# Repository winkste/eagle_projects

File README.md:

# eagle_projects
eagle projects for several different targets

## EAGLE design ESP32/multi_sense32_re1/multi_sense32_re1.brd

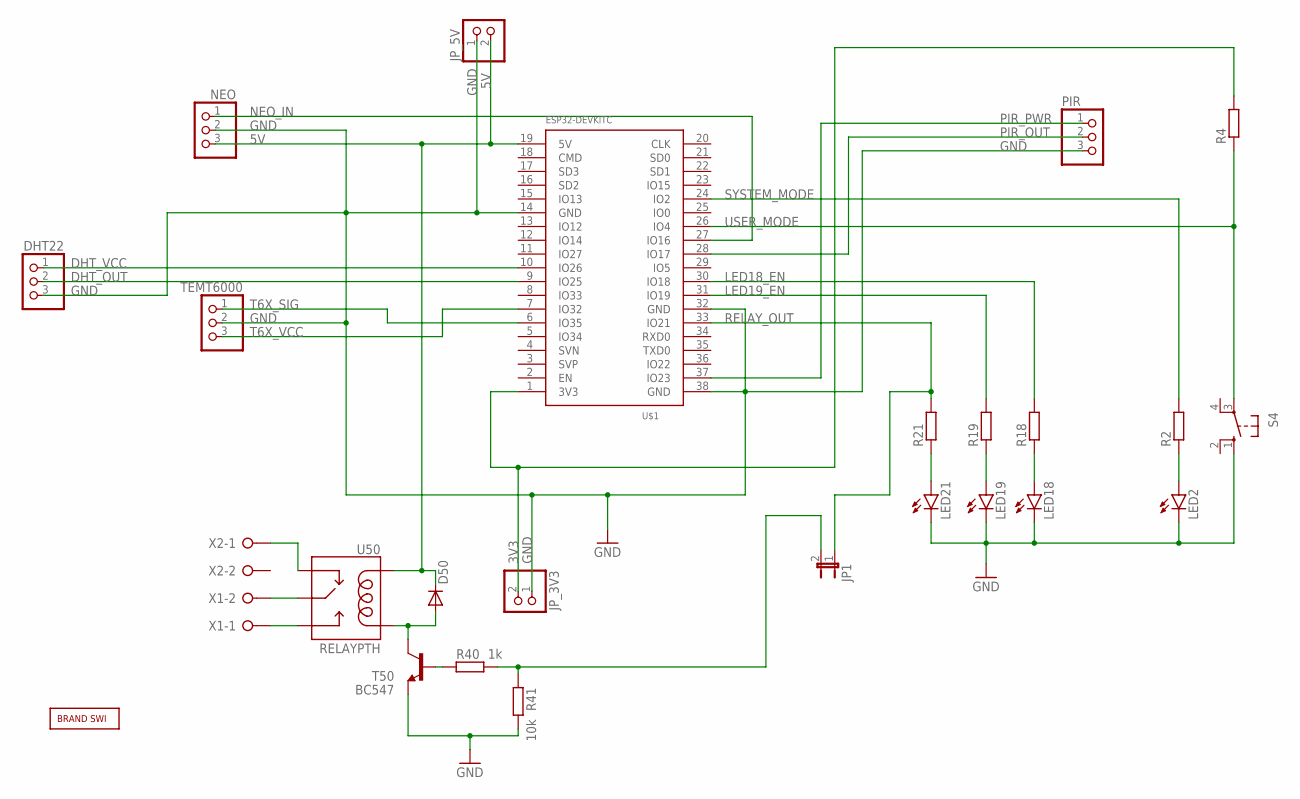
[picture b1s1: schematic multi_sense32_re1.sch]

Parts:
D50: 1N4148DO35-7; DO35-7
DHT22: PINHD-1X3; 1X03
JP1: JP1E; JP1
JP_3V3, JP_5V: PINHD-1X2; 1X02
LED2, LED18, LED19, LED21: LEDCHIPLED_1206; CHIPLED_1206
NEO: PINHD-1X3; 1X03
PIR: PINHD-1X3; 1X03
R2, R4, R18, R19, R21: R-EU_R1206; R1206
R40: 1k; 0207/10
R41: 10k; 0207/10
S4: 10-XX; B3F-10XX
T50: BC547; TO92
TEMT6000: PINHD-1X3; 1X03
U50: RELAYPTH; SRD-05VDC-SL-C
U$1: ESP32DEVKITC; ESP32-DEVKITC
U$2: BRAND_SWI5X7; BRAND_SWI_5X7
X1, X2: W237-02P; W237-132

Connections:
3V3: JP_3V3.2, R4.2, U$1.1 (3V3)
5V: D50.C, JP_5V.2, NEO.3, U50.COIL1, U$1.19 (5V)
DHT_OUT: DHT22.2, U$1.9 (IO25)
DHT_VCC: DHT22.1, U$1.10 (IO26)
GND: DHT22.3, JP_3V3.1, JP_5V.1, LED2.C, LED18.C, LED19.C, LED21.C, NEO.2, PIR.3, R41.2, S4.1 (S), T50.1 (E), TEMT6000.2, U$1.14 (GND), U$1.32 (GND), U$1.38 (GND)
LED18_EN: R18.2, U$1.30 (IO18)
LED19_EN: R19.2, U$1.31 (IO19)
LED21_EN: JP1.2, R40.2, R41.1
unnamed: U50.SWOPEN, X1.1
unnamed: LED21.A, R21.1
unnamed: U50.SWCOMMON, X1.2
unnamed: LED19.A, R19.1
unnamed: LED18.A, R18.1
unnamed: U50.SWCLOSED (SWCLOSE), X2.1
unnamed: LED2.A, R2.1
unnamed: D50.A, T50.3 (C), U50.COIL0
unnamed: R40.1, T50.2 (B)
NEO_IN: NEO.1, U$1.27 (IO16)
PIR_OUT: PIR.2, U$1.28 (IO17)
PIR_PWR: PIR.1, U$1.37 (IO23)
RELAY_OUT: JP1.1, R21.2, U$1.33 (IO21)
SYSTEM_MODE: R2.2, U$1.24 (IO2)
T6X_SIG: TEMT6000.1, U$1.6 (IO35)
T6X_VCC: TEMT6000.3, U$1.7 (IO32)
USER_MODE: R4.1, S4.3, U$1.26 (IO4)

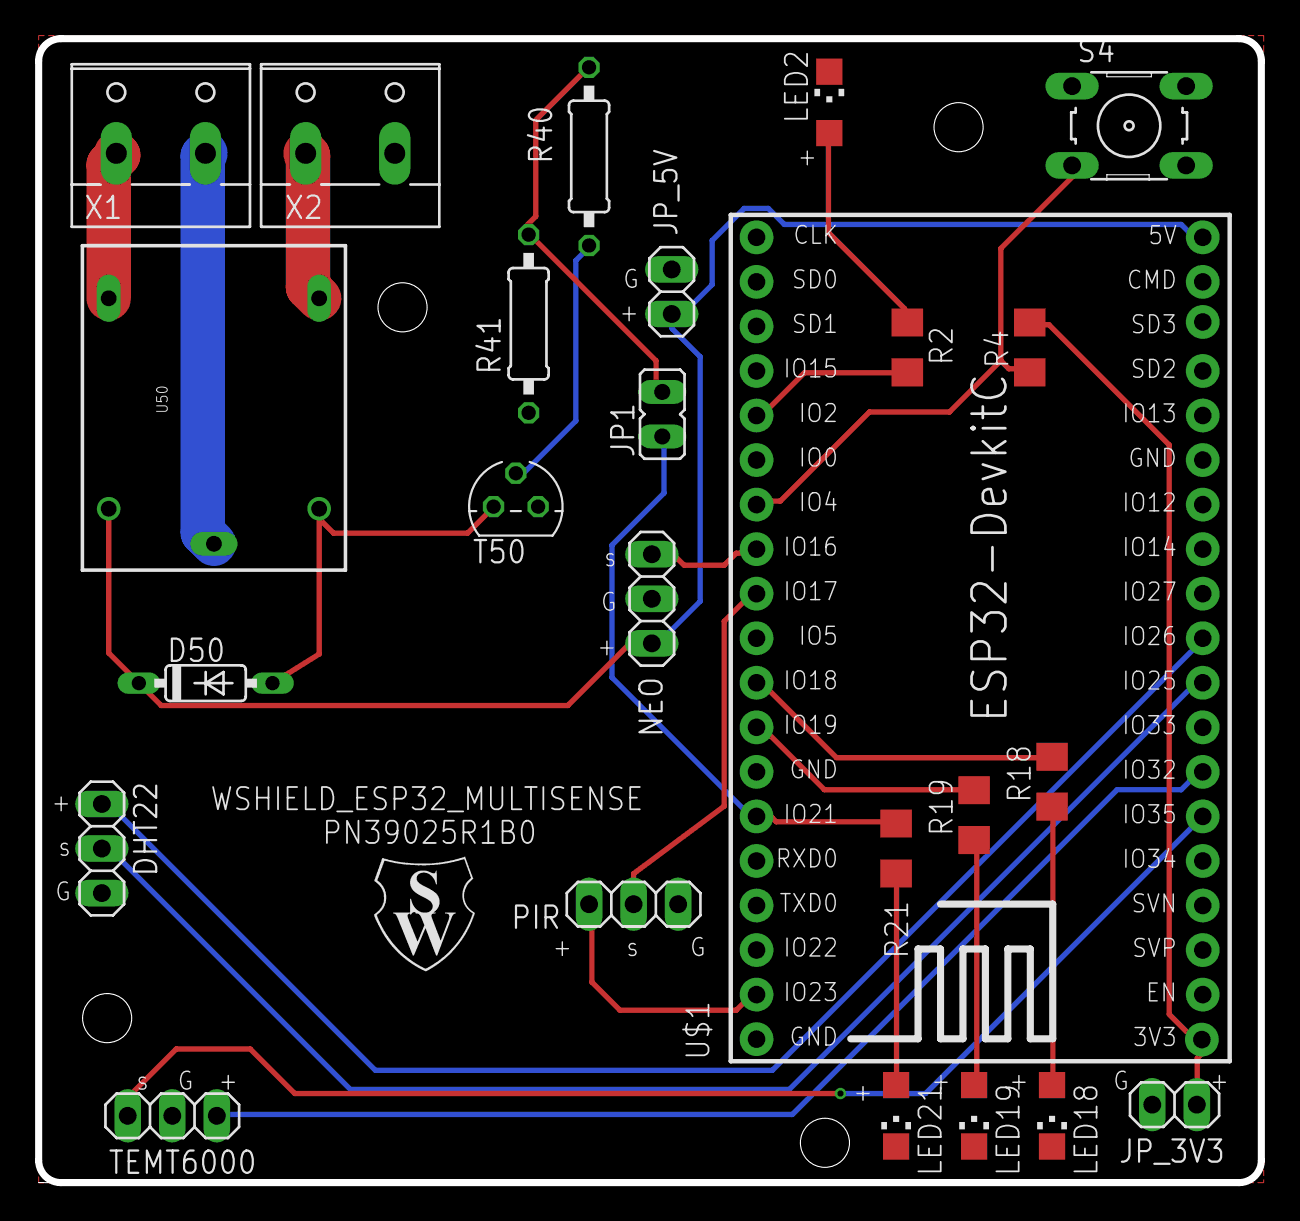
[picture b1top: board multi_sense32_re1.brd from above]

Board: 2 copper layers, 69.7 x 65.2 mm, 26 parts (0 on the bottom side), 25 nets.

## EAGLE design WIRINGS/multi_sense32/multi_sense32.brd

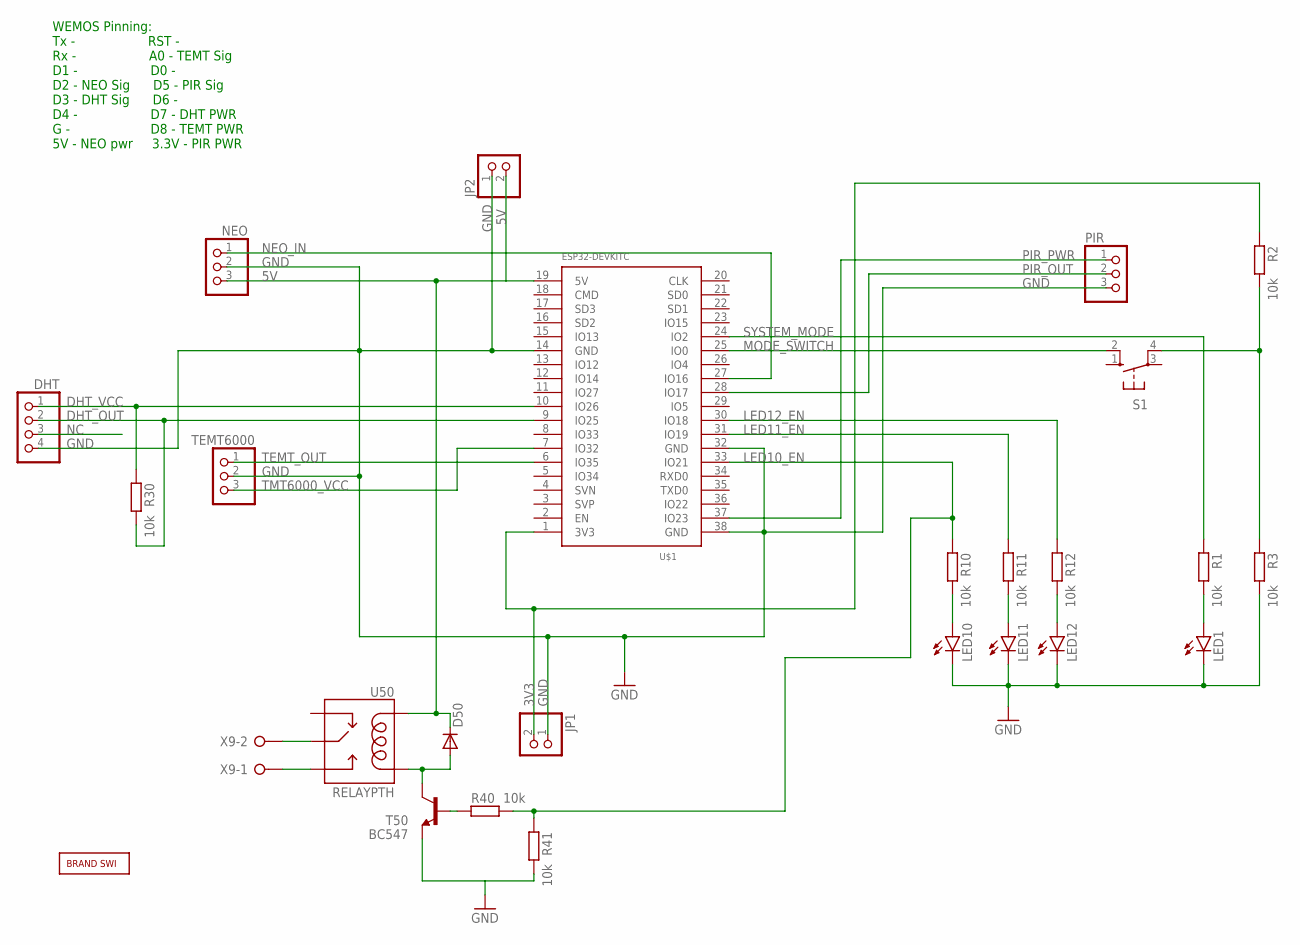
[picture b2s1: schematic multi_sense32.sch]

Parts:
D50: 1N4148DO35-7; DO35-7
DHT: PINHD-1X4; 1X04
JP1, JP2: PINHD-1X2; 1X02
LED1, LED10, LED11, LED12: LED3MM
NEO: PINHD-1X3; 1X03
PIR: PINHD-1X3; 1X03
R1, R2, R3, R10, R11, R12, R30, R40, R41: 10k; 0207/10
S1: 10-XX; B3F-10XX
T50: BC547; TO92
TEMT6000: PINHD-1X3; 1X03
U50: RELAYPTH; SRD-05VDC-SL-C
U$1: ESP32DEVKITC; ESP32-DEVKITC
U$2: BRAND_SWI5X7; BRAND_SWI_5X7
X9: W237-02P; W237-132

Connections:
3V3: JP1.2, R2.1, U$1.1 (3V3)
5V: D50.C, JP2.2, NEO.3, U50.COIL1, U$1.19 (5V)
DHT_OUT: DHT.2, R30.2, U$1.9 (IO25)
DHT_VCC: DHT.1, R30.1, U$1.10 (IO26)
GND: DHT.4, JP1.1, JP2.1, LED1.K (C), LED10.K (C), LED11.K (C), LED12.K (C), NEO.2, PIR.3, R3.2, R41.2, T50.1 (E), TEMT6000.2, U$1.14 (GND), U$1.32 (GND), U$1.38 (GND)
LED10_EN: R10.1, R40.2, R41.1, U$1.33 (IO21)
LED11_EN: R11.1, U$1.31 (IO19)
LED12_EN: R12.1, U$1.30 (IO18)
MODE_SWITCH: S1.2 (S1), U$1.25 (IO0)
unnamed: U50.SWOPEN, X9.1
unnamed: LED10.A, R10.2
unnamed: U50.SWCOMMON, X9.2
unnamed: LED11.A, R11.2
unnamed: LED12.A, R12.2
unnamed: R2.2, R3.1, S1.4 (P1)
unnamed: LED1.A, R1.2
unnamed: D50.A, T50.3 (C), U50.COIL0
unnamed: R40.1, T50.2 (B)
NC: DHT.3
NEO_IN: NEO.1, U$1.27 (IO16)
PIR_OUT: PIR.2, U$1.28 (IO17)
PIR_PWR: PIR.1, U$1.37 (IO23)
SYSTEM_MODE: R1.1, U$1.24 (IO2)
TEMT_OUT: TEMT6000.1, U$1.6 (IO35)
TMT6000_VCC: TEMT6000.3, U$1.7 (IO32)

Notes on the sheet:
WEMOS Pinning: Tx - RST - Rx - A0 - TEMT Sig D1 - D0 - D2 - NEO Sig D5 - PIR Sig D3 - DHT Sig D6 - D4 - D7 - DHT PWR G - D8 - TEMT PWR 5V - NEO pwr 3.3V - PIR PWR

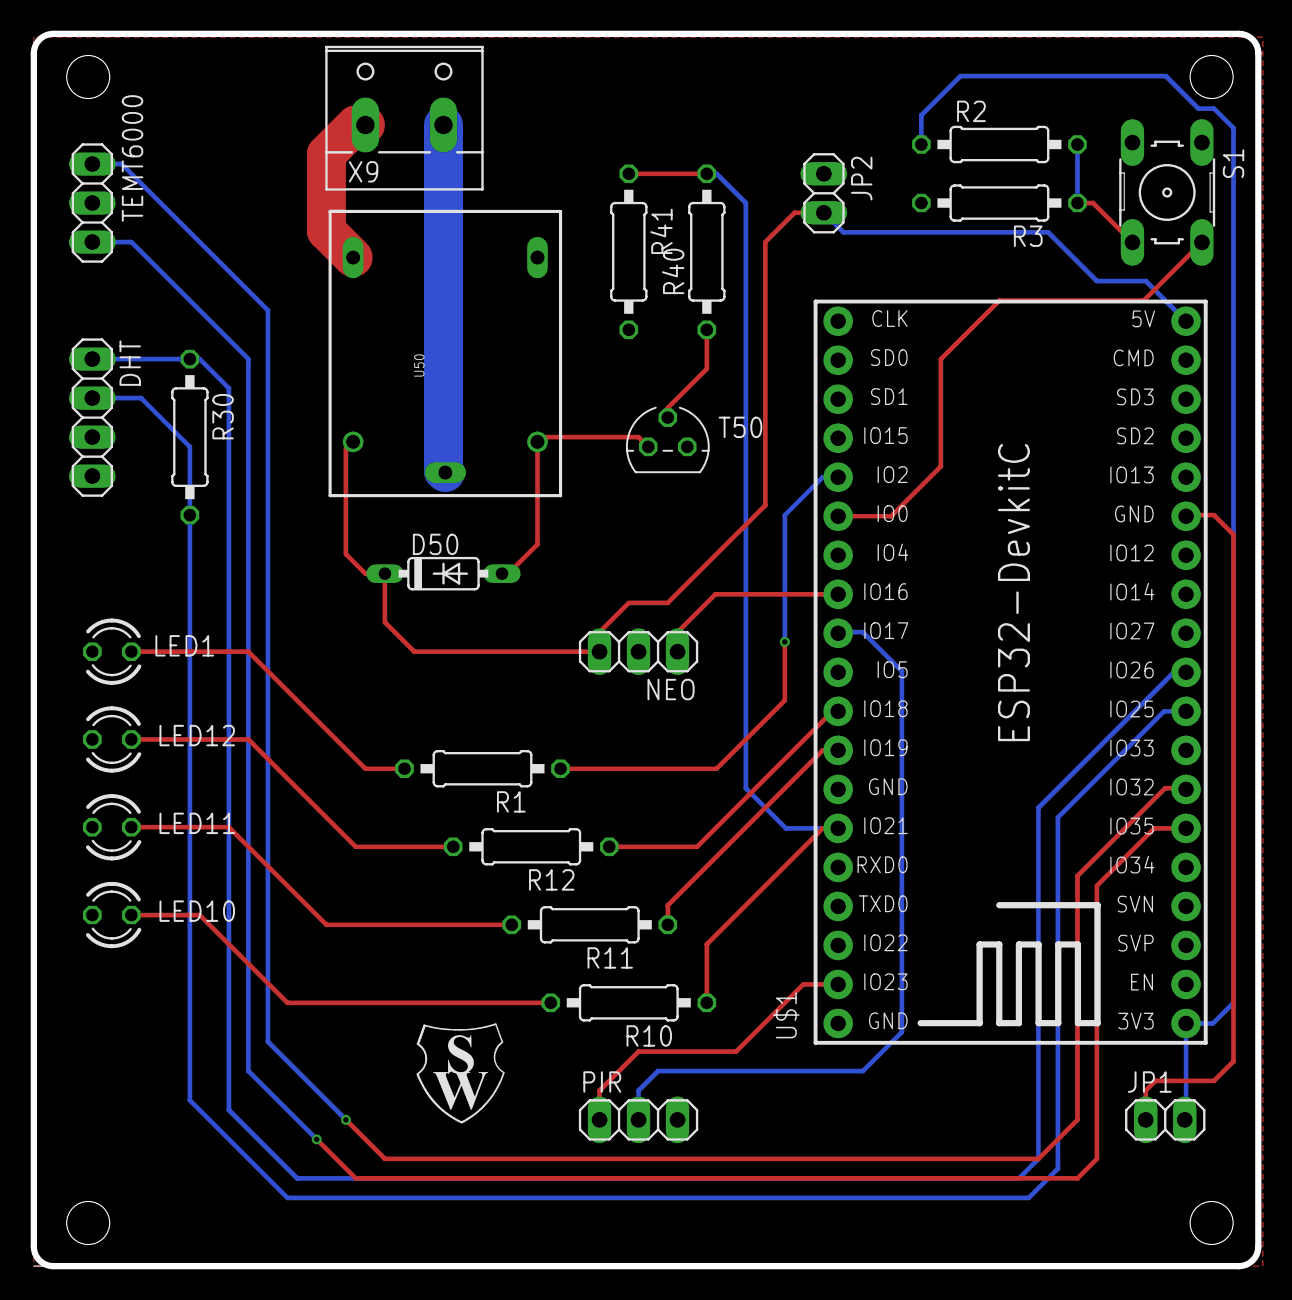
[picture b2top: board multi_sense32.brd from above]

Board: 2 copper layers, 79.7 x 80.2 mm, 26 parts (0 on the bottom side), 24 nets.

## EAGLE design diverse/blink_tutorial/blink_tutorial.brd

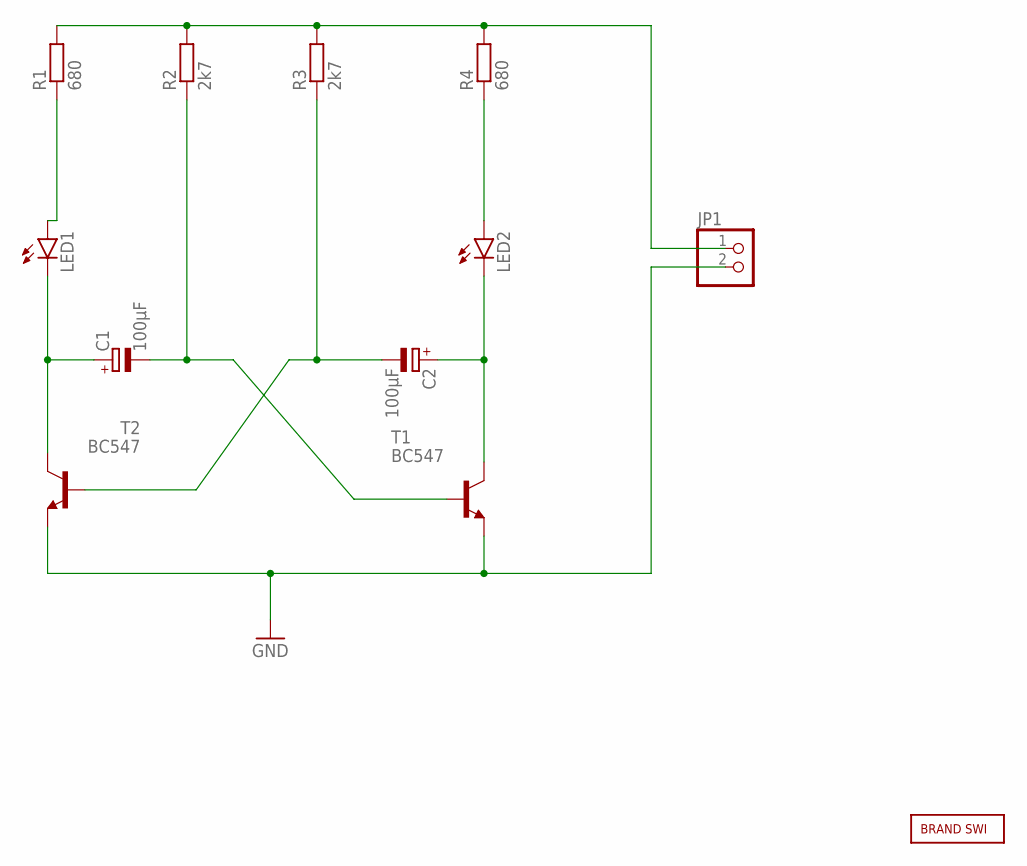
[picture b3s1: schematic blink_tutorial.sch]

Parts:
C1, C2: 100µF; E2,5-6
JP1: PINHD-1X2; 1X02
LED1, LED2: LED5MM
R1, R4: 680; M1206
R2, R3: 2k7; M1206
T1, T2: BC547; TO92
U$1: SIG1; BRAND_SWI_5X7

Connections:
GND: JP1.2, T1.1 (E), T2.1 (E)
unnamed: JP1.1, R1.2, R2.2, R3.2, R4.2
unnamed: LED1.A, R1.1
unnamed: LED2.A, R4.1
unnamed: C1.+, LED1.K (C), T2.3 (C)
unnamed: C2.+, LED2.K (C), T1.3 (C)
unnamed: C2.-, R3.1, T2.2 (B)
unnamed: C1.-, R2.1, T1.2 (B)

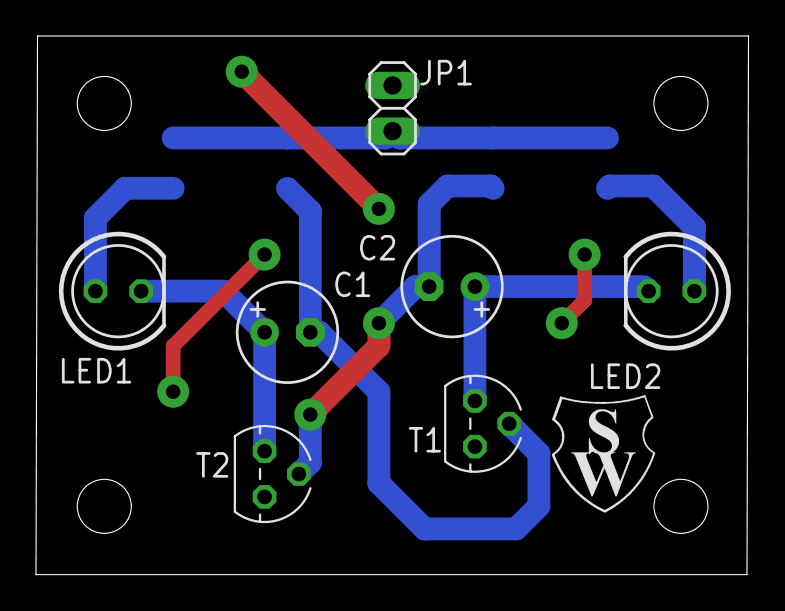
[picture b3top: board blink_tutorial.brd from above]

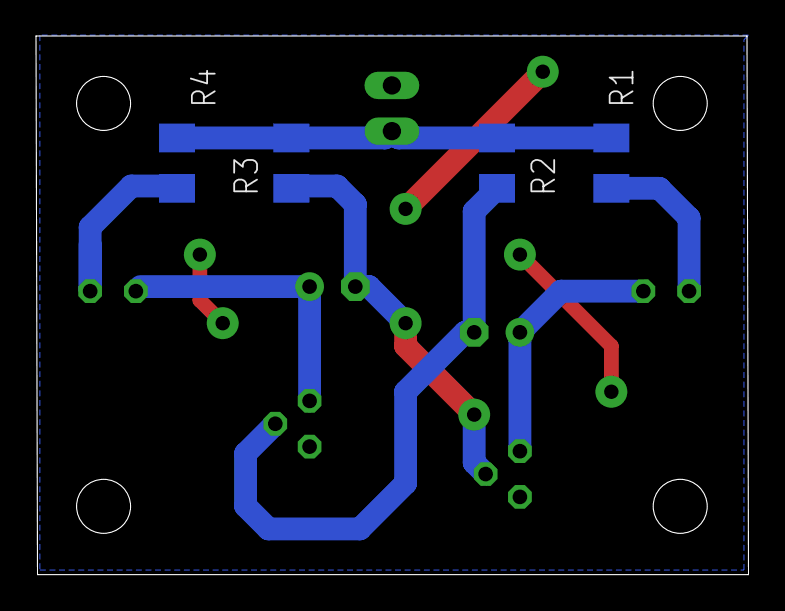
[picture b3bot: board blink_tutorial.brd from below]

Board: 2 copper layers, 39.6 x 29.9 mm, 12 parts (4 on the bottom side), 8 nets.

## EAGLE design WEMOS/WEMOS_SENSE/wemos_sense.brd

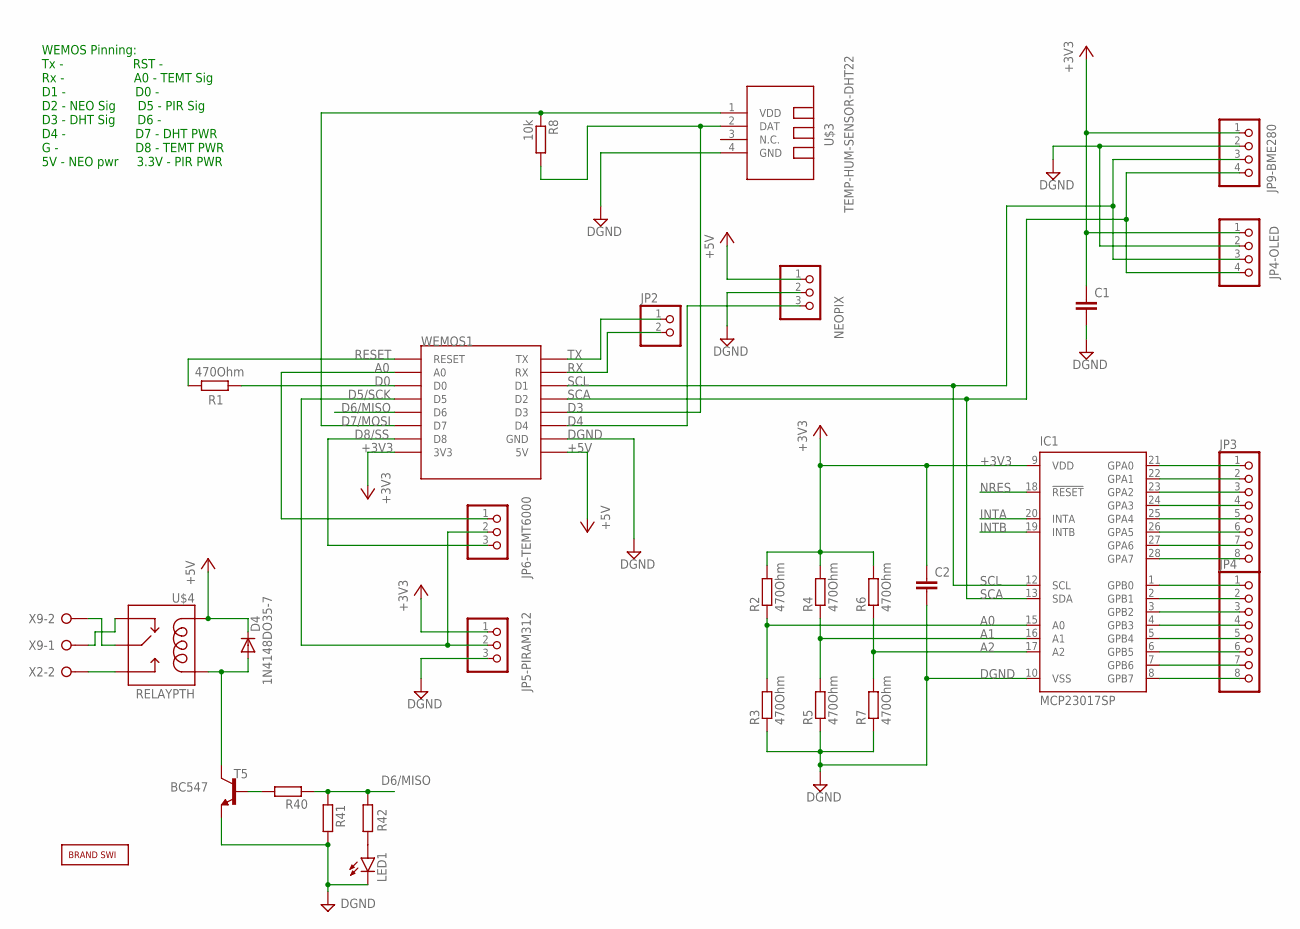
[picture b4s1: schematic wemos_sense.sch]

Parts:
C1, C2: C-EUC1210; C1210
D4: 1N4148DO35-7; DO35-7
IC1: MCP23017SP; DIL28-3
JP2: PINHD-1X2; 1X02
JP3, JP4: PINHD-1X8; 1X08
JP4-OLED, JP9-BME280: PINHD-1X4; 1X04
JP5-PIRAM312, JP6-TEMT6000: PINHD-1X3; 1X03
LED1: LED3MM
NEOPIX: PINHD-1X3; 1X03
R1, R2, R3, R4, R5, R6, R7: 470Ohm; R0805
R8: 10k; R0805
R40, R41, R42: R-EU_R0805; R0805
T5: BC547; TO92
U$2: BRAND_SWI5X7; BRAND_SWI_5X7
U$3: TEMP-HUM-SENSOR-DHT22
U$4: RELAYPTH; SRD-05VDC-SL-C
WEMOS1: WEMOS-D1-MINI
X2, X9: W237-02P; W237-132

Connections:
+3V3: C1.1, C2.1, IC1.9 (VDD), JP4-OLED.1, JP5-PIRAM312.1, JP9-BME280.1, R2.2, R4.2, R6.2, WEMOS1.3V3
+5V: D4.C, NEOPIX.1, U$4.COIL1, WEMOS1.5V
A0: IC1.15 (A0), JP6-TEMT6000.1, R2.1, R3.2, WEMOS1.A0
A1: IC1.16 (A1), R4.1, R5.2
A2: IC1.17 (A2), R6.1, R7.2
D0: R1.2, WEMOS1.D0
D3: R8.2, U$3.2 (DAT), WEMOS1.D3
D4: NEOPIX.3, WEMOS1.D4
D5/SCK: JP5-PIRAM312.2, JP6-TEMT6000.2, WEMOS1.D5
D6/MISO: R40.1, R41.1, R42.2, WEMOS1.D6
D7/MOSI: R8.1, U$3.1 (VDD), WEMOS1.D7
D8/SS: JP6-TEMT6000.3, WEMOS1.D8
DGND: C1.2, C2.2, IC1.10 (VSS), JP4-OLED.2, JP5-PIRAM312.3, JP9-BME280.2, LED1.K (C), NEOPIX.2, R3.1, R5.1, R7.1, R41.2, T5.1 (E), U$3.4 (GND), WEMOS1.GND
INTA: IC1.20 (INTA)
INTB: IC1.19 (INTB)
unnamed: IC1.21 (GPA0), JP3.1
unnamed: IC1.22 (GPA1), JP3.2
unnamed: IC1.23 (GPA2), JP3.3
unnamed: IC1.24 (GPA3), JP3.4
unnamed: IC1.25 (GPA4), JP3.5
unnamed: IC1.26 (GPA5), JP3.6
unnamed: IC1.27 (GPA6), JP3.7
unnamed: IC1.28 (GPA7), JP3.8
unnamed: IC1.1 (GPB0), JP4.1
unnamed: IC1.2 (GPB1), JP4.2
unnamed: IC1.3 (GPB2), JP4.3
unnamed: IC1.4 (GPB3), JP4.4
unnamed: IC1.5 (GPB4), JP4.5
unnamed: IC1.6 (GPB5), JP4.6
unnamed: IC1.7 (GPB6), JP4.7
unnamed: IC1.8 (GPB7), JP4.8
unnamed: U$4.SWCOMMON, X9.2
unnamed: U$4.SWCLOSED (SWCLOSE), X9.1
unnamed: LED1.A, R42.1
unnamed: D4.A, T5.3 (C), U$4.COIL0
unnamed: U$4.SWOPEN, X2.2
unnamed: R40.2, T5.2 (B)
NRES: IC1.18 (!RESET)
RESET: R1.1, WEMOS1.RESET
RX: JP2.2, WEMOS1.RX
SCA: IC1.13 (SDA), JP4-OLED.4, JP9-BME280.4, WEMOS1.D2
SCL: IC1.12 (SCL), JP4-OLED.3, JP9-BME280.3, WEMOS1.D1
TX: JP2.1, WEMOS1.TX

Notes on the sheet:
WEMOS Pinning: Tx - RST - Rx - A0 - TEMT Sig D1 - D0 - D2 - NEO Sig D5 - PIR Sig D3 - DHT Sig D6 - D4 - D7 - DHT PWR G - D8 - TEMT PWR 5V - NEO pwr 3.3V - PIR PWR

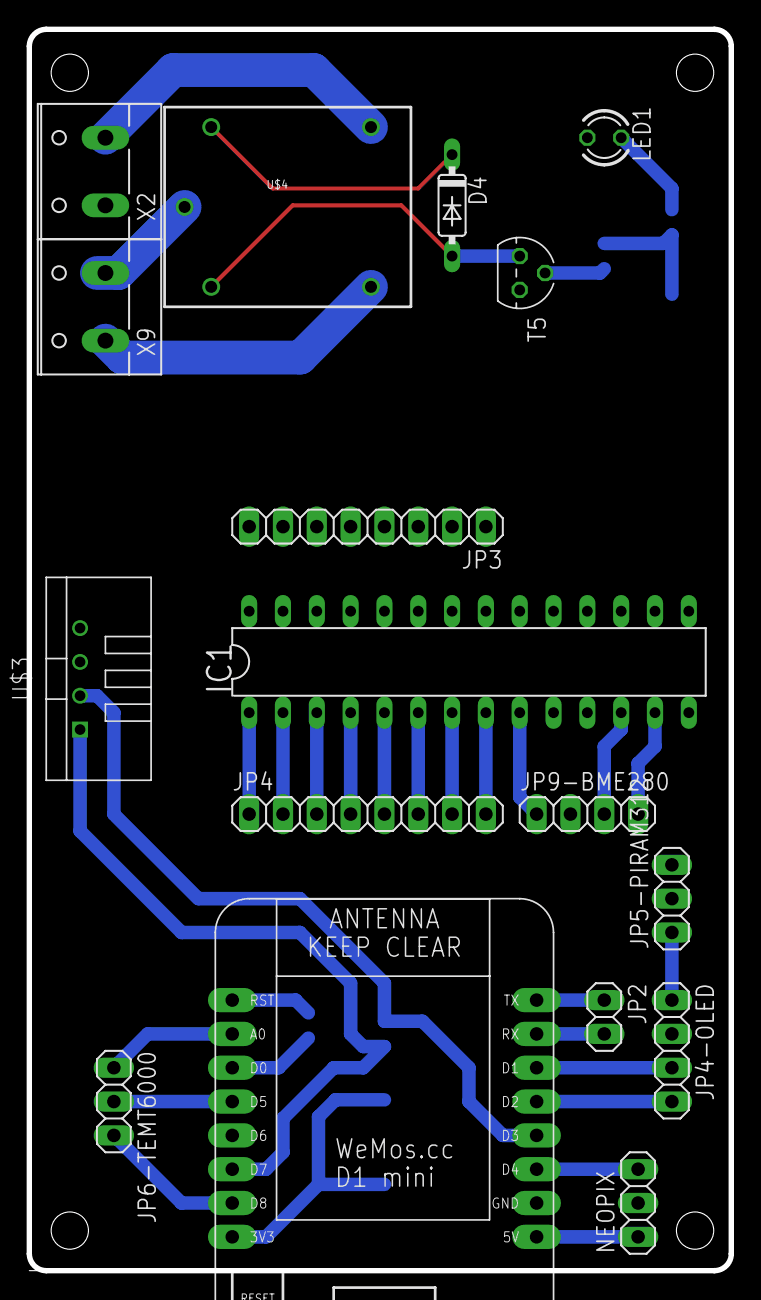
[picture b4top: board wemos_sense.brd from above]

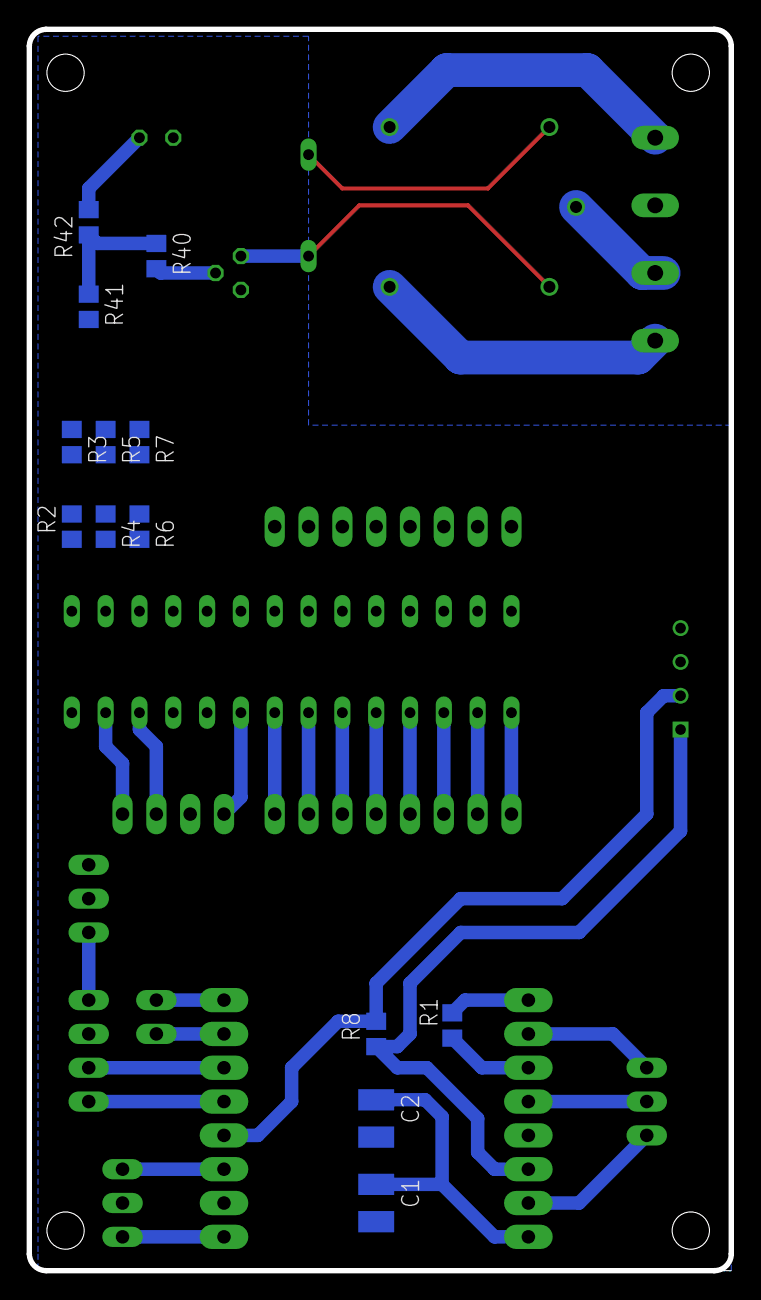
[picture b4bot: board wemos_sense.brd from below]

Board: 2 copper layers, 52.7 x 93.2 mm, 31 parts (13 on the bottom side), 40 nets.

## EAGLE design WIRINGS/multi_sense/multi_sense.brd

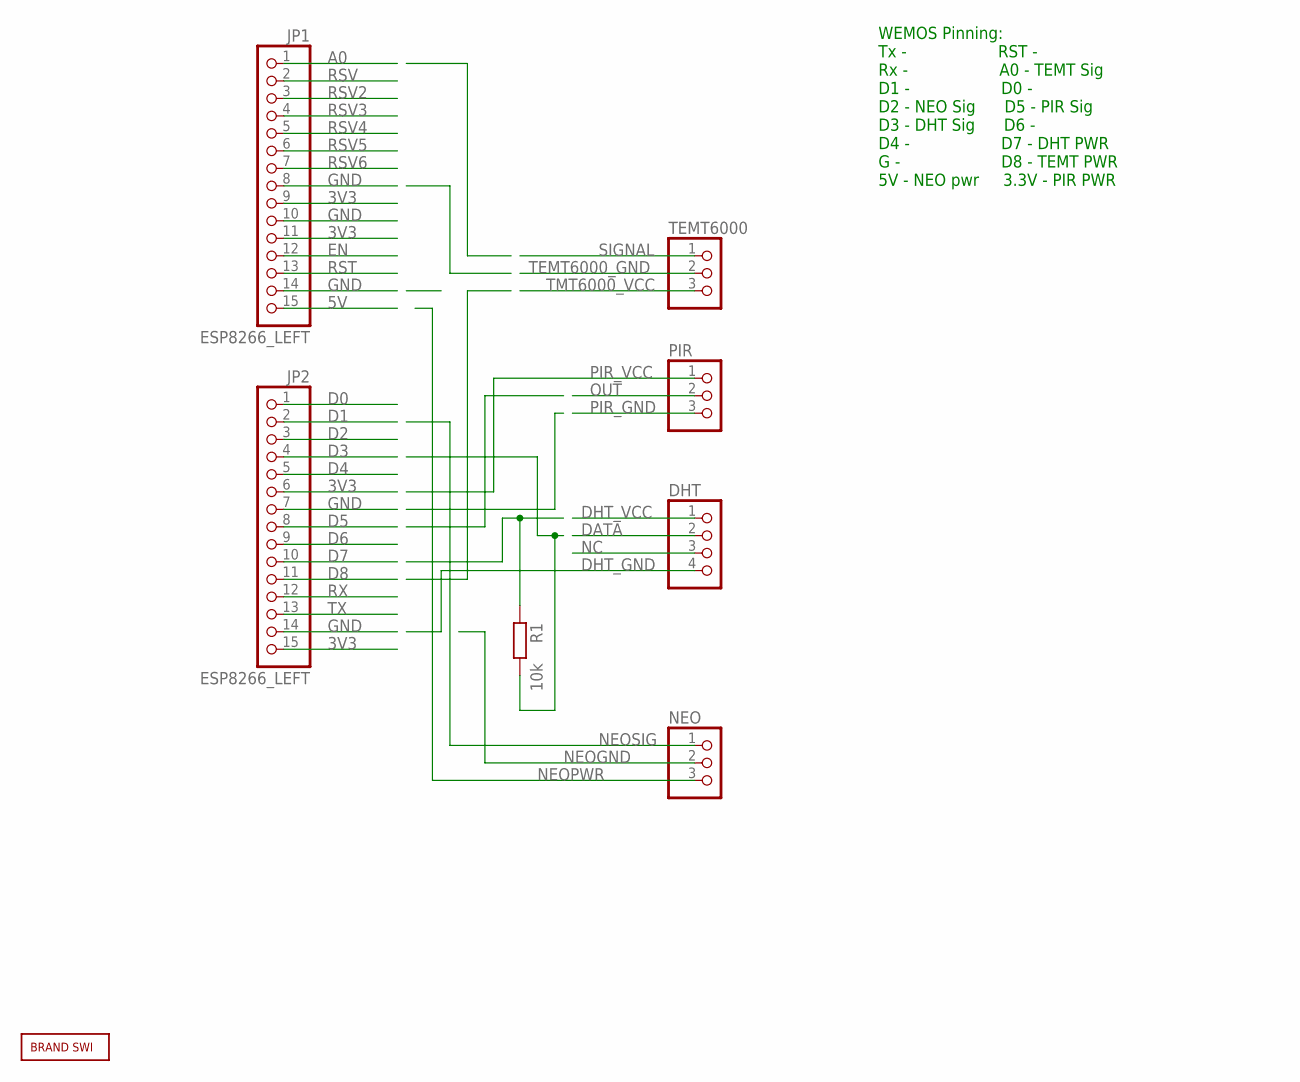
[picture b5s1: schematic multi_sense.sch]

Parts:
DHT: PINHD-1X4; 1X04
JP1, JP2: ESP8266_LEFT; 1X15
NEO: PINHD-1X3; 1X03
PIR: PINHD-1X3; 1X03
R1: 10k; 0207/10
TEMT6000: PINHD-1X3; 1X03
U$2: BRAND_SWI5X7; BRAND_SWI_5X7

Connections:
3V3: JP1.9, JP1.11, JP2.6, JP2.15
5V: JP1.15
A0: JP1.1
D0: JP2.1
D1: JP2.2
D2: JP2.3
D3: JP2.4
D4: JP2.5
D5: JP2.8
D6: JP2.9
D7: JP2.10
D8: JP2.11
DATA: DHT.2
DHT_GND: DHT.4
DHT_VCC: DHT.1
EN: JP1.12
GND: JP1.8, JP1.10, JP1.14, JP2.7, JP2.14
NC: DHT.3
NEOGND: NEO.2
NEOPWR: NEO.3
NEOSIG: NEO.1
OUT: PIR.2
PIR_GND: PIR.3
PIR_VCC: PIR.1
RST: JP1.13
RSV: JP1.2
RSV2: JP1.3
RSV3: JP1.4
RSV4: JP1.5
RSV5: JP1.6
RSV6: JP1.7
RX: JP2.12
SIGNAL: TEMT6000.1
TEMT6000_GND: TEMT6000.2
TMT6000_VCC: TEMT6000.3
TX: JP2.13

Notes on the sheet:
WEMOS Pinning: Tx - RST - Rx - A0 - TEMT Sig D1 - D0 - D2 - NEO Sig D5 - PIR Sig D3 - DHT Sig D6 - D4 - D7 - DHT PWR G - D8 - TEMT PWR 5V - NEO pwr 3.3V - PIR PWR

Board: 2 copper layers, 8 parts (1 on the bottom side), 2 nets, no tracks yet.

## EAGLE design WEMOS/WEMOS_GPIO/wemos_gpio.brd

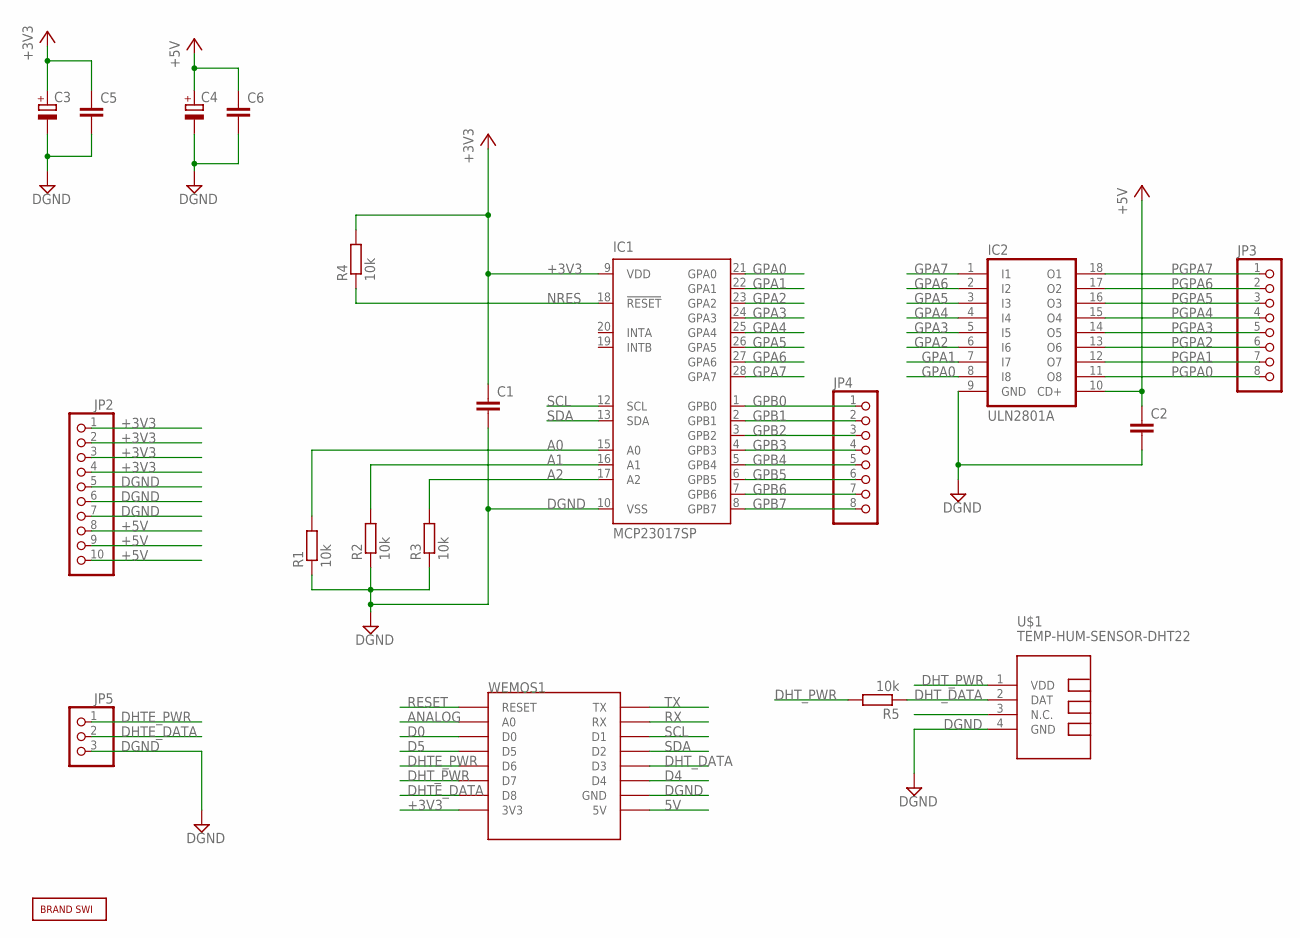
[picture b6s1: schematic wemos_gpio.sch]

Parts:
C1, C2, C5, C6: C-EUC1210; C1210
C3, C4: CPOL-EUTT5D7; TT5D7
IC1: MCP23017SP; DIL28-3
IC2: ULN2801A; DIL18
JP2: PINHD-1X10; 1X10
JP3, JP4: PINHD-1X8; 1X08
JP5: PINHD-1X3; 1X03
R1, R2, R3, R4, R5: 10k; M1206
U$1: TEMP-HUM-SENSOR-DHT22
U$2: BRAND_SWI5X7; BRAND_SWI_5X7
WEMOS1: WEMOS-D1-MINI

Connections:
5V: WEMOS1.5V
+3V3: C1.1, C3.+, C5.1, IC1.9 (VDD), JP2.1, JP2.2, JP2.3, JP2.4, R4.2, WEMOS1.3V3
+5V: C2.1, C4.+, C6.1, IC2.10 (CD+), JP2.8, JP2.9, JP2.10
A0: IC1.15 (A0), R1.2
A1: IC1.16 (A1), R2.2
A2: IC1.17 (A2), R3.2
ANALOG: WEMOS1.A0
D0: WEMOS1.D0
D4: WEMOS1.D4
D5: WEMOS1.D5
DGND: C1.2, C2.2, C3.-, C4.-, C5.2, C6.2, IC1.10 (VSS), IC2.9 (GND), JP2.5, JP2.6, JP2.7, JP5.3, R1.1, R2.1, R3.1, U$1.4 (GND), WEMOS1.GND
DHTE_DATA: JP5.2, WEMOS1.D8
DHTE_PWR: JP5.1, WEMOS1.D6
DHT_DATA: R5.1, U$1.2 (DAT), WEMOS1.D3
DHT_PWR: R5.2, U$1.1 (VDD), WEMOS1.D7
GPA0: IC1.21 (GPA0), IC2.8 (I8)
GPA1: IC1.22 (GPA1), IC2.7 (I7)
GPA2: IC1.23 (GPA2), IC2.6 (I6)
GPA3: IC1.24 (GPA3), IC2.5 (I5)
GPA4: IC1.25 (GPA4), IC2.4 (I4)
GPA5: IC1.26 (GPA5), IC2.3 (I3)
GPA6: IC1.27 (GPA6), IC2.2 (I2)
GPA7: IC1.28 (GPA7), IC2.1 (I1)
GPB0: IC1.1 (GPB0), JP4.1
GPB1: IC1.2 (GPB1), JP4.2
GPB2: IC1.3 (GPB2), JP4.3
GPB3: IC1.4 (GPB3), JP4.4
GPB4: IC1.5 (GPB4), JP4.5
GPB5: IC1.6 (GPB5), JP4.6
GPB6: IC1.7 (GPB6), JP4.7
GPB7: IC1.8 (GPB7), JP4.8
NRES: IC1.18 (!RESET), R4.1
PGPA0: IC2.11 (O8), JP3.8
PGPA1: IC2.12 (O7), JP3.7
PGPA2: IC2.13 (O6), JP3.6
PGPA3: IC2.14 (O5), JP3.5
PGPA4: IC2.15 (O4), JP3.4
PGPA5: IC2.16 (O3), JP3.3
PGPA6: IC2.17 (O2), JP3.2
PGPA7: IC2.18 (O1), JP3.1
RESET: WEMOS1.RESET
RX: WEMOS1.RX
SCL: IC1.12 (SCL), WEMOS1.D1
SDA: IC1.13 (SDA), WEMOS1.D2

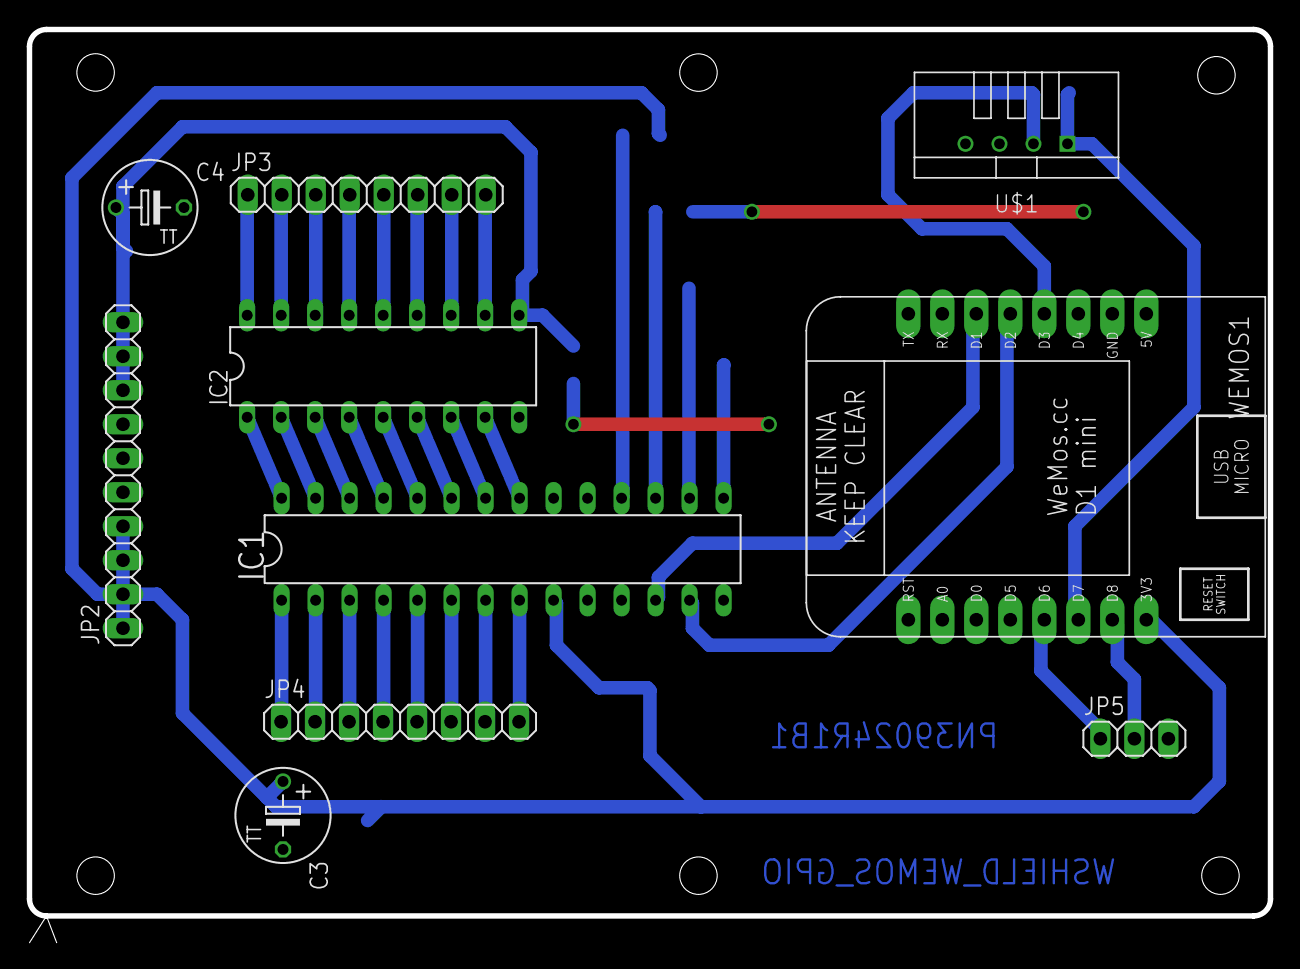
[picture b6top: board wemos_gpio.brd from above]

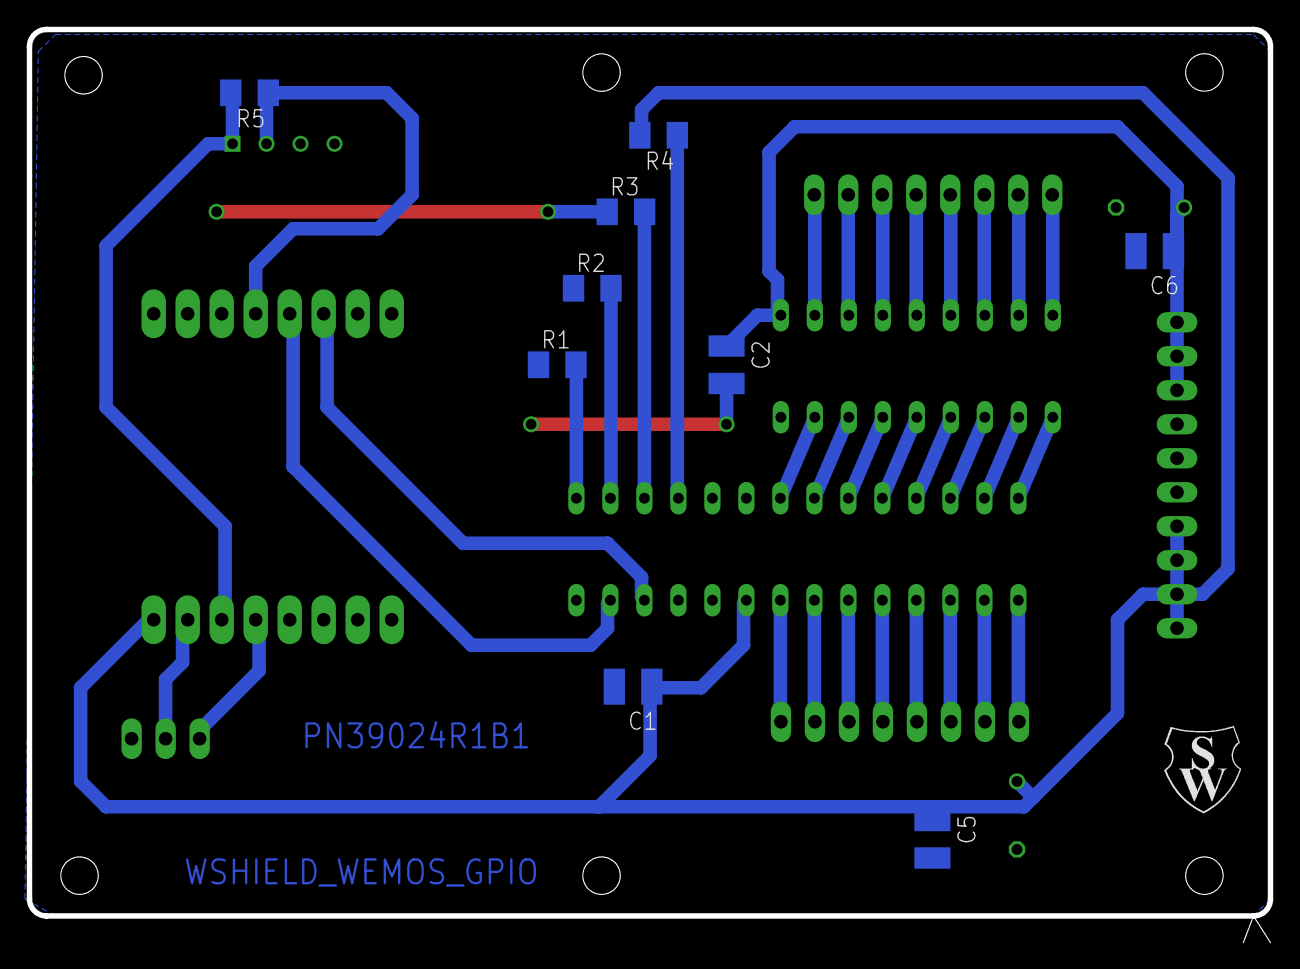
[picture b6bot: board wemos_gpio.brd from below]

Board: 2 copper layers, 92.7 x 68.0 mm, 20 parts (10 on the bottom side), 37 nets.

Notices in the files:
parts and their libraries:
diy-modules: Released under the Creative Commons Attribution 4.0 International License: http://creativecommons.org/licenses/by/4.0
